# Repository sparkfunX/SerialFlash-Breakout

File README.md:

SerialFlash-Breakout
========================================

[*Serial Flash Breakout - Assembled*](https://www.sparkfun.com/products/17115)

[*Serial Flash Breakout - Bare*](https://www.sparkfun.com/products/17116)

Serial flash chips are everywhere and they're as useful as they are ubiquitous. If you've never used a serial flash device in your own projects, you should try it, because it's very handy to have a place to store things that don't fit in program memory. Things like sensor readings, long strings, and error logs can be hard to stow away on platforms that don't have a ton of in-built storage, which is where serial flash comes in. Simply write all of that data out over SPI for the flash chip to hold on to and retrieve it later! And thanks to their ubiquity, these chips have been largely standardized not only in terms of their software interface but also their hardware footprint, so there are plenty of serial flash chips to choose from.

SparkFun labored with love to design this board. Feel like supporting open source hardware? 
Buy a [board](https://www.sparkfun.com/products/17115) from SparkFun!

Repository Contents
-------------------

* **/Hardware** - Eagle design files (.brd, .sch)
* **/Documents** - Datasheet
* **/Production** - Production design files

License Information
-------------------

This product is _**open source**_! 

Please review the LICENSE.md file for license information. 

If you have any questions or concerns on licensing, please contact technical support on our [SparkFun forums](https://forum.sparkfun.com/viewforum.php?f=152).

Distributed as-is; no warranty is given.

- Your friends at SparkFun.

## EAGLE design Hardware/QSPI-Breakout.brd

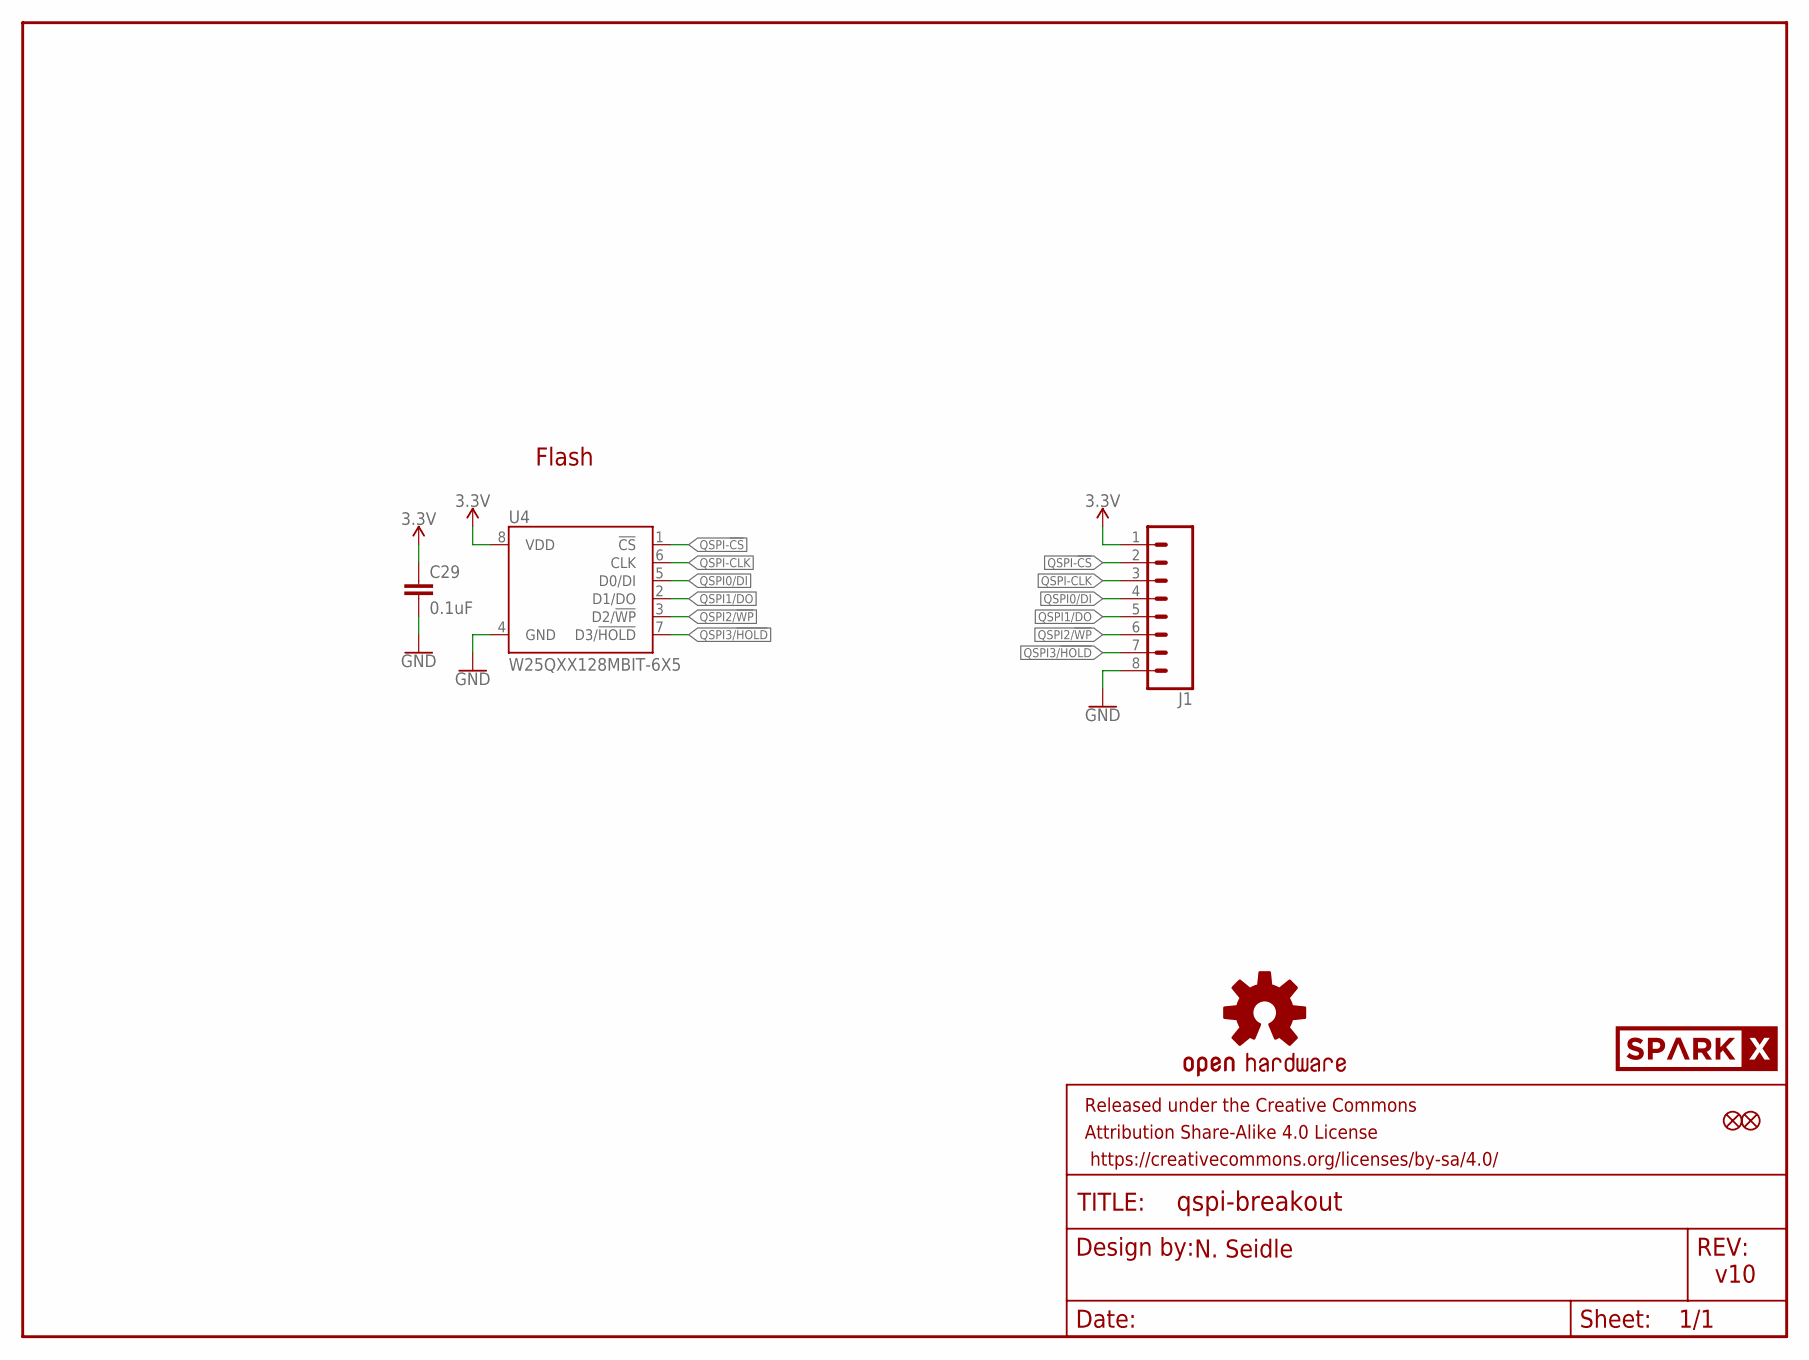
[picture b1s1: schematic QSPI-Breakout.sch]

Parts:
C29: 0.1uF; 0603
FD1, FD2: FIDUCIALUFIDUCIAL; FIDUCIAL-MICRO
FRAME2: FRAME-LETTER; CREATIVE_COMMONS
J1: CONN_08NO_SILK_DNP; 1X08_NO_SILK
LOGO2: OSHW-LOGONO_SILK; DUMMY
U4: W25QXX128MBIT-6X5; WSON-8-6X5-SKINNY_CENTERPAD
U$3: SPARKX-LOGO4; SPARKX-MEDIUM

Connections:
3.3V: C29.1, J1.1, U4.8 (VDD)
GND: C29.2, J1.8, U4.4 (GND)
QSPI0/DI: J1.4, U4.5 (D0/DI)
QSPI1/DO: J1.5, U4.2 (D1/DO)
QSPI2/!WP!: J1.6, U4.3 (D2/!WP!)
QSPI3/!HOLD!: J1.7, U4.7 (D3/!HOLD!)
QSPI-!CS!: J1.2, U4.1 (!CS!)
QSPI-CLK: J1.3, U4.6 (CLK)

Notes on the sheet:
v10
N. Seidle
Flash

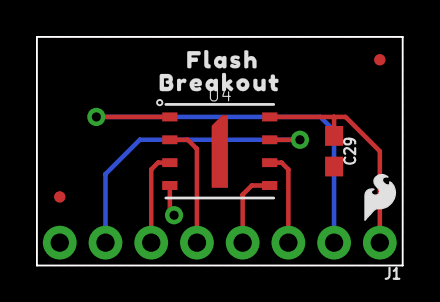
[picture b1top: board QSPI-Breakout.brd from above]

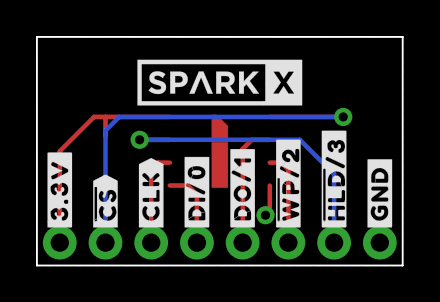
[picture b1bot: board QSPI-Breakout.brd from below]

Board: 2 copper layers, 20.3 x 12.7 mm, 19 parts (9 on the bottom side), 8 nets.

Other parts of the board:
U$1: BREAKOUT1
U$2: FLASH0
U$4: ##HLD##3#2
U$5: ##WP##2#3
U$6: SFE_LOGO_FLAME_.1
U$7: #3#3V#1
U$8: #CLK#6
U$9: #DI#0#5
U$10: #DO#1#4
U$11: #GND#0
U$12: ##CS##7

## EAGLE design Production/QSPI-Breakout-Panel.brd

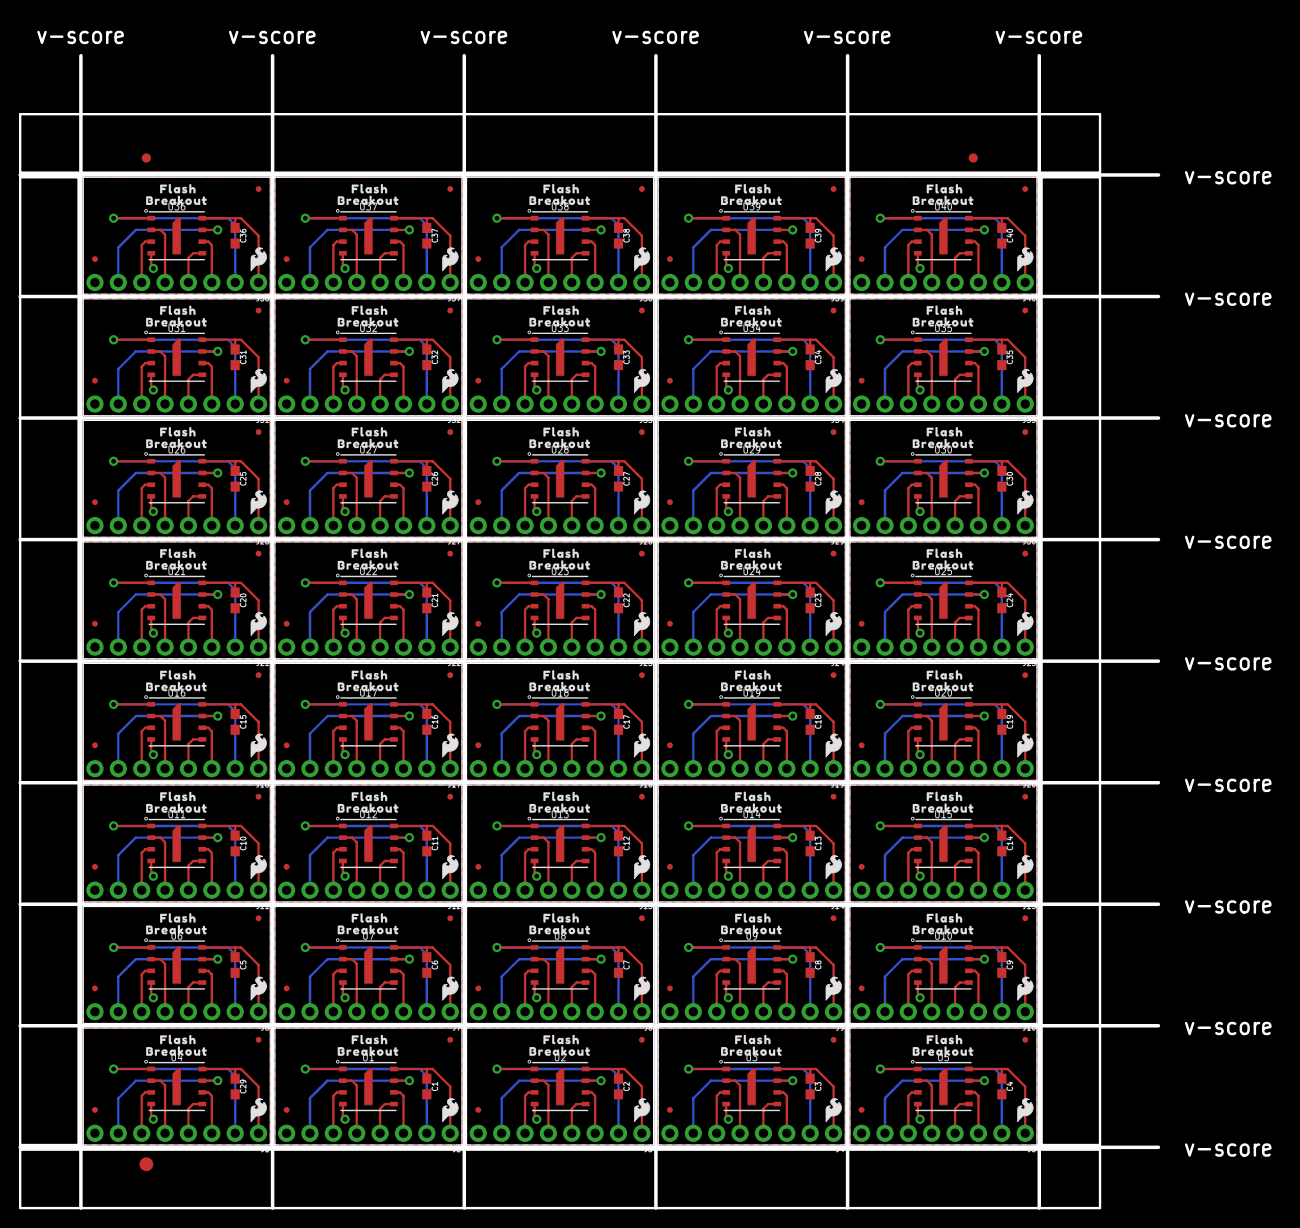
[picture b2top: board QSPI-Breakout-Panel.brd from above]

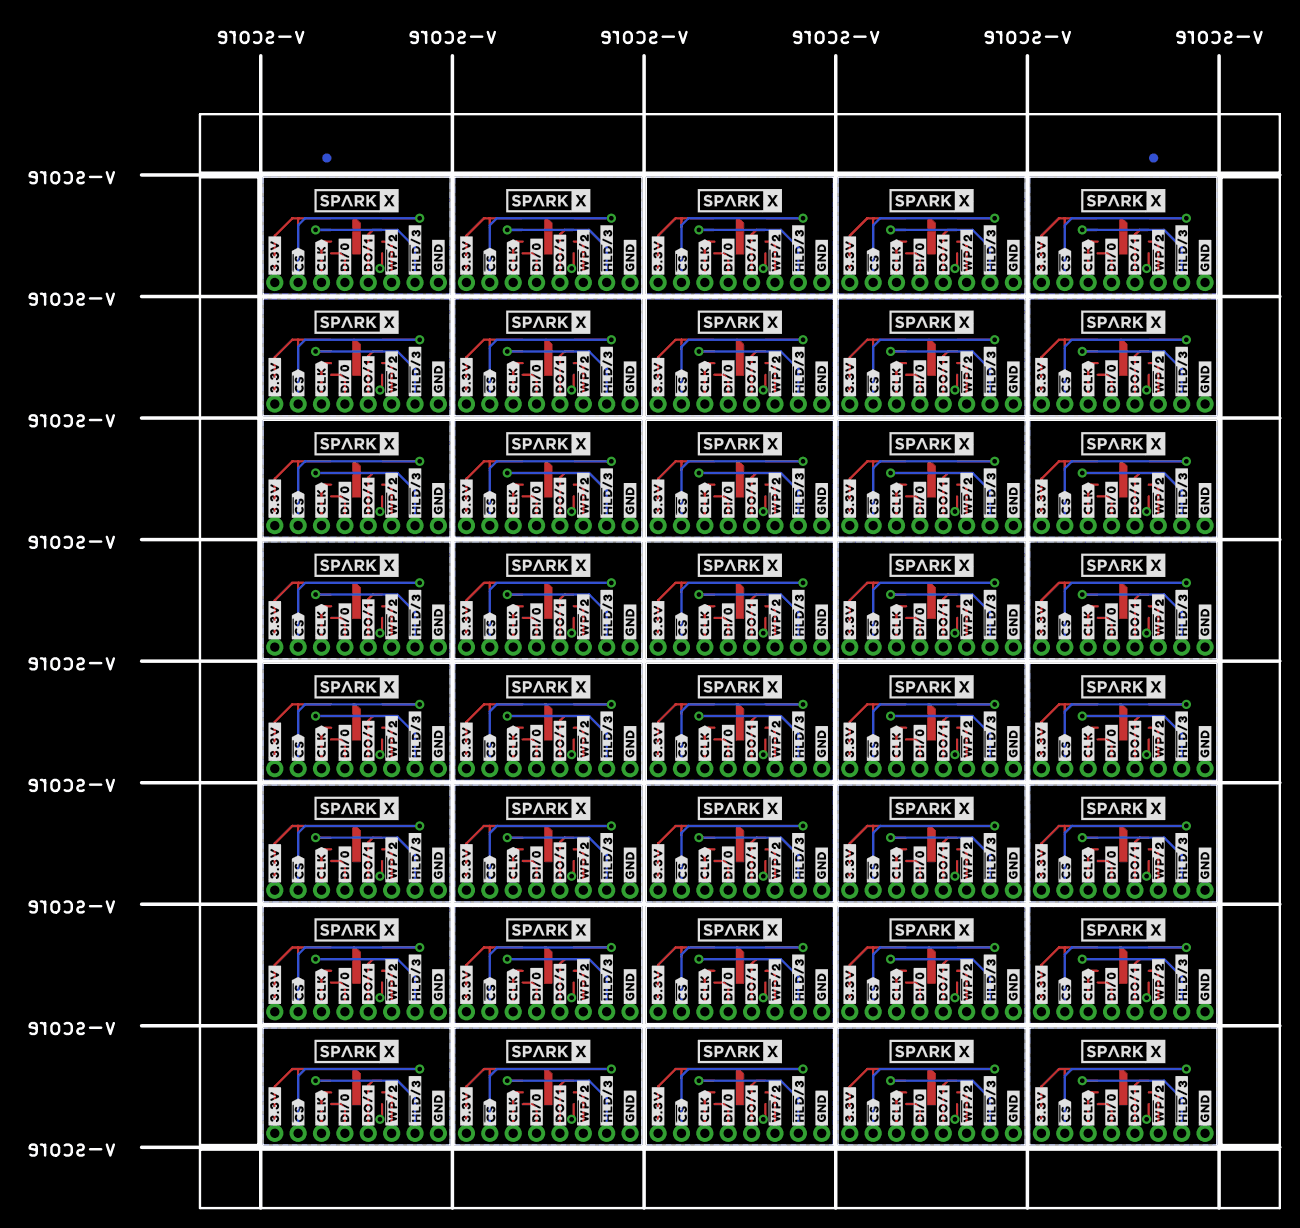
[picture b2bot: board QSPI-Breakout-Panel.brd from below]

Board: 2 copper layers, 123.7 x 125.2 mm, 725 parts (362 on the bottom side), 320 nets.

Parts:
C1, C2, C3, C4, C5, C6, C7, C8, C9, C10, C11, C12, C13, C14, C15, C16, C17, C18, C19, C20, C21, C22, C23, C24, C25, C26, C27, C28, C29, C30, C31, C32, C33, C34, C35, C36, C37, C38, C39, C40: 0.1uF; 0603
E$1, E$2, E$3, E$4: FIDUCIAL-1X2
E$5: FIDUCIAL-1.5X3
FD1, FD2, FD3, FD4, FD5, FD6, FD7, FD8, FD9, FD10, FD11, FD12, FD13, FD14, FD15, FD16, FD17, FD18, FD19, FD20, FD21, FD22, FD23, FD24, FD25, FD26, FD27, FD28, FD29, FD30, FD31, FD32, FD33, FD34, FD35, FD36, FD37, FD38, FD39, FD40, FD41, FD42, FD43, FD44, FD45, FD46, FD47, FD48, FD49, FD50, FD51, FD52, FD53, FD54, FD55, FD56, FD57, FD58, FD59, FD60, FD61, FD62, FD63, FD64, FD65, FD66, FD67, FD68, FD69, FD70, FD71, FD72, FD73, FD74, FD75, FD76, FD77, FD78, FD79, FD80: FIDUCIALUFIDUCIAL; FIDUCIAL-MICRO
J1, J2, J3, J4, J5, J6, J7, J8, J9, J10, J11, J12, J13, J14, J15, J16, J17, J18, J19, J20, J21, J22, J23, J24, J25, J26, J27, J28, J29, J30, J31, J32, J33, J34, J35, J36, J37, J38, J39, J40: 1X08_NO_SILK
LOGO1, LOGO2, LOGO3, LOGO4, LOGO5, LOGO6, LOGO7, LOGO8, LOGO9, LOGO10, LOGO11, LOGO12, LOGO13, LOGO14, LOGO15, LOGO16, LOGO17, LOGO18, LOGO19, LOGO20, LOGO21, LOGO22, LOGO23, LOGO24, LOGO25, LOGO26, LOGO27, LOGO28, LOGO29, LOGO30, LOGO31, LOGO32, LOGO33, LOGO34, LOGO35, LOGO36, LOGO37, LOGO38, LOGO39, LOGO40: OSHW-LOGONO_SILK; DUMMY
U1, U2, U3, U4, U5, U6, U7, U8, U9, U10, U11, U12, U13, U14, U15, U16, U17, U18, U19, U20, U21, U22, U23, U24, U25, U26, U27, U28, U29, U30, U31, U32, U33, U34, U35, U36, U37, U38, U39, U40: W25QXX128MBIT-6X5; WSON-8-6X5-SKINNY_CENTERPAD
U$1, U$14, U$26, U$38, U$50, U$62, U$74, U$86, U$98, U$110, U$122, U$134, U$146, U$158, U$170, U$182, U$194, U$206, U$218, U$230, U$242, U$254, U$266, U$278, U$290, U$302, U$314, U$326, U$338, U$350, U$362, U$374, U$386, U$398, U$410, U$422, U$434, U$446, U$458, U$470: BREAKOUT1
U$2, U$15, U$27, U$39, U$51, U$63, U$75, U$87, U$99, U$111, U$123, U$135, U$147, U$159, U$171, U$183, U$195, U$207, U$219, U$231, U$243, U$255, U$267, U$279, U$291, U$303, U$315, U$327, U$339, U$351, U$363, U$375, U$387, U$399, U$411, U$423, U$435, U$447, U$459, U$471: FLASH0
U$3, U$24, U$36, U$48, U$60, U$72, U$84, U$96, U$108, U$120, U$132, U$144, U$156, U$168, U$180, U$192, U$204, U$216, U$228, U$240, U$252, U$264, U$276, U$288, U$300, U$312, U$324, U$336, U$348, U$360, U$372, U$384, U$396, U$408, U$420, U$432, U$444, U$456, U$468, U$480: SPARKX-LOGO4; SPARKX-MEDIUM
U$4, U$16, U$28, U$40, U$52, U$64, U$76, U$88, U$100, U$112, U$124, U$136, U$148, U$160, U$172, U$184, U$196, U$208, U$220, U$232, U$244, U$256, U$268, U$280, U$292, U$304, U$316, U$328, U$340, U$352, U$364, U$376, U$388, U$400, U$412, U$424, U$436, U$448, U$460, U$472: ##HLD##3#2
U$5, U$17, U$29, U$41, U$53, U$65, U$77, U$89, U$101, U$113, U$125, U$137, U$149, U$161, U$173, U$185, U$197, U$209, U$221, U$233, U$245, U$257, U$269, U$281, U$293, U$305, U$317, U$329, U$341, U$353, U$365, U$377, U$389, U$401, U$413, U$425, U$437, U$449, U$461, U$473: ##WP##2#3
U$6, U$13, U$25, U$37, U$49, U$61, U$73, U$85, U$97, U$109, U$121, U$133, U$145, U$157, U$169, U$181, U$193, U$205, U$217, U$229, U$241, U$253, U$265, U$277, U$289, U$301, U$313, U$325, U$337, U$349, U$361, U$373, U$385, U$397, U$409, U$421, U$433, U$445, U$457, U$469: SFE_LOGO_FLAME_.1
U$7, U$18, U$30, U$42, U$54, U$66, U$78, U$90, U$102, U$114, U$126, U$138, U$150, U$162, U$174, U$186, U$198, U$210, U$222, U$234, U$246, U$258, U$270, U$282, U$294, U$306, U$318, U$330, U$342, U$354, U$366, U$378, U$390, U$402, U$414, U$426, U$438, U$450, U$462, U$474: #3#3V#1
U$8, U$19, U$31, U$43, U$55, U$67, U$79, U$91, U$103, U$115, U$127, U$139, U$151, U$163, U$175, U$187, U$199, U$211, U$223, U$235, U$247, U$259, U$271, U$283, U$295, U$307, U$319, U$331, U$343, U$355, U$367, U$379, U$391, U$403, U$415, U$427, U$439, U$451, U$463, U$475: #CLK#6
U$9, U$20, U$32, U$44, U$56, U$68, U$80, U$92, U$104, U$116, U$128, U$140, U$152, U$164, U$176, U$188, U$200, U$212, U$224, U$236, U$248, U$260, U$272, U$284, U$296, U$308, U$320, U$332, U$344, U$356, U$368, U$380, U$392, U$404, U$416, U$428, U$440, U$452, U$464, U$476: #DI#0#5
U$10, U$21, U$33, U$45, U$57, U$69, U$81, U$93, U$105, U$117, U$129, U$141, U$153, U$165, U$177, U$189, U$201, U$213, U$225, U$237, U$249, U$261, U$273, U$285, U$297, U$309, U$321, U$333, U$345, U$357, U$369, U$381, U$393, U$405, U$417, U$429, U$441, U$453, U$465, U$477: #DO#1#4
U$11, U$22, U$34, U$46, U$58, U$70, U$82, U$94, U$106, U$118, U$130, U$142, U$154, U$166, U$178, U$190, U$202, U$214, U$226, U$238, U$250, U$262, U$274, U$286, U$298, U$310, U$322, U$334, U$346, U$358, U$370, U$382, U$394, U$406, U$418, U$430, U$442, U$454, U$466, U$478: #GND#0
U$12, U$23, U$35, U$47, U$59, U$71, U$83, U$95, U$107, U$119, U$131, U$143, U$155, U$167, U$179, U$191, U$203, U$215, U$227, U$239, U$251, U$263, U$275, U$287, U$299, U$311, U$323, U$335, U$347, U$359, U$371, U$383, U$395, U$407, U$419, U$431, U$443, U$455, U$467, U$479: ##CS##7

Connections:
3.3V: C29.1, J1.1, U4.8
3.3V1: C1.1, J2.1, U1.8
3.3V2: C2.1, J3.1, U2.8
3.3V3: C3.1, J4.1, U3.8
3.3V4: C4.1, J5.1, U5.8
3.3V5: C5.1, J6.1, U6.8
3.3V6: C6.1, J7.1, U7.8
3.3V7: C7.1, J8.1, U8.8
3.3V8: C8.1, J9.1, U9.8
3.3V9: C9.1, J10.1, U10.8
3.3V10: C10.1, J11.1, U11.8
3.3V11: C11.1, J12.1, U12.8
3.3V12: C12.1, J13.1, U13.8
3.3V13: C13.1, J14.1, U14.8
3.3V14: C14.1, J15.1, U15.8
3.3V15: C15.1, J16.1, U16.8
3.3V16: C16.1, J17.1, U17.8
3.3V17: C17.1, J18.1, U18.8
3.3V18: C18.1, J19.1, U19.8
3.3V19: C19.1, J20.1, U20.8
3.3V20: C20.1, J21.1, U21.8
3.3V21: C21.1, J22.1, U22.8
3.3V22: C22.1, J23.1, U23.8
3.3V23: C23.1, J24.1, U24.8
3.3V24: C24.1, J25.1, U25.8
3.3V25: C25.1, J26.1, U26.8
3.3V26: C26.1, J27.1, U27.8
3.3V27: C27.1, J28.1, U28.8
3.3V28: C28.1, J29.1, U29.8
3.3V29: C30.1, J30.1, U30.8
3.3V30: C31.1, J31.1, U31.8
3.3V31: C32.1, J32.1, U32.8
3.3V32: C33.1, J33.1, U33.8
3.3V33: C34.1, J34.1, U34.8
3.3V34: C35.1, J35.1, U35.8
3.3V35: C36.1, J36.1, U36.8
3.3V36: C37.1, J37.1, U37.8
3.3V37: C38.1, J38.1, U38.8
3.3V38: C39.1, J39.1, U39.8
3.3V39: C40.1, J40.1, U40.8
GND: C29.2, J1.8, U4.4
GND1: C1.2, J2.8, U1.4
GND2: C2.2, J3.8, U2.4
GND3: C3.2, J4.8, U3.4
GND4: C4.2, J5.8, U5.4
GND5: C5.2, J6.8, U6.4
GND6: C6.2, J7.8, U7.4
GND7: C7.2, J8.8, U8.4
GND8: C8.2, J9.8, U9.4
GND9: C9.2, J10.8, U10.4
GND10: C10.2, J11.8, U11.4
GND11: C11.2, J12.8, U12.4
GND12: C12.2, J13.8, U13.4
GND13: C13.2, J14.8, U14.4
GND14: C14.2, J15.8, U15.4
GND15: C15.2, J16.8, U16.4
GND16: C16.2, J17.8, U17.4
GND17: C17.2, J18.8, U18.4
GND18: C18.2, J19.8, U19.4
GND19: C19.2, J20.8, U20.4
GND20: C20.2, J21.8, U21.4
GND21: C21.2, J22.8, U22.4
GND22: C22.2, J23.8, U23.4
GND23: C23.2, J24.8, U24.4
GND24: C24.2, J25.8, U25.4
GND25: C25.2, J26.8, U26.4
GND26: C26.2, J27.8, U27.4
GND27: C27.2, J28.8, U28.4
GND28: C28.2, J29.8, U29.4
GND29: C30.2, J30.8, U30.4
GND30: C31.2, J31.8, U31.4
GND31: C32.2, J32.8, U32.4
GND32: C33.2, J33.8, U33.4
GND33: C34.2, J34.8, U34.4
GND34: C35.2, J35.8, U35.4
GND35: C36.2, J36.8, U36.4
GND36: C37.2, J37.8, U37.4
GND37: C38.2, J38.8, U38.4
GND38: C39.2, J39.8, U39.4
GND39: C40.2, J40.8, U40.4
QSPI0/DI: J1.4, U4.5
QSPI0/DI1: J2.4, U1.5
QSPI0/DI2: J3.4, U2.5
QSPI0/DI3: J4.4, U3.5
QSPI0/DI4: J5.4, U5.5
QSPI0/DI5: J6.4, U6.5
QSPI0/DI6: J7.4, U7.5
QSPI0/DI7: J8.4, U8.5
QSPI0/DI8: J9.4, U9.5
QSPI0/DI9: J10.4, U10.5
QSPI0/DI10: J11.4, U11.5
QSPI0/DI11: J12.4, U12.5
QSPI0/DI12: J13.4, U13.5
QSPI0/DI13: J14.4, U14.5
QSPI0/DI14: J15.4, U15.5
QSPI0/DI15: J16.4, U16.5
QSPI0/DI16: J17.4, U17.5
QSPI0/DI17: J18.4, U18.5
QSPI0/DI18: J19.4, U19.5
QSPI0/DI19: J20.4, U20.5
QSPI0/DI20: J21.4, U21.5
QSPI0/DI21: J22.4, U22.5
QSPI0/DI22: J23.4, U23.5
QSPI0/DI23: J24.4, U24.5
QSPI0/DI24: J25.4, U25.5
QSPI0/DI25: J26.4, U26.5
QSPI0/DI26: J27.4, U27.5
QSPI0/DI27: J28.4, U28.5
QSPI0/DI28: J29.4, U29.5
QSPI0/DI29: J30.4, U30.5
QSPI0/DI30: J31.4, U31.5
QSPI0/DI31: J32.4, U32.5
QSPI0/DI32: J33.4, U33.5
QSPI0/DI33: J34.4, U34.5
QSPI0/DI34: J35.4, U35.5
QSPI0/DI35: J36.4, U36.5
QSPI0/DI36: J37.4, U37.5
QSPI0/DI37: J38.4, U38.5
QSPI0/DI38: J39.4, U39.5
QSPI0/DI39: J40.4, U40.5
QSPI1/DO: J1.5, U4.2
QSPI1/DO1: J2.5, U1.2
QSPI1/DO2: J3.5, U2.2
QSPI1/DO3: J4.5, U3.2
QSPI1/DO4: J5.5, U5.2
QSPI1/DO5: J6.5, U6.2
QSPI1/DO6: J7.5, U7.2
QSPI1/DO7: J8.5, U8.2
QSPI1/DO8: J9.5, U9.2
QSPI1/DO9: J10.5, U10.2
QSPI1/DO10: J11.5, U11.2
QSPI1/DO11: J12.5, U12.2
QSPI1/DO12: J13.5, U13.2
QSPI1/DO13: J14.5, U14.2
QSPI1/DO14: J15.5, U15.2
QSPI1/DO15: J16.5, U16.2
QSPI1/DO16: J17.5, U17.2
QSPI1/DO17: J18.5, U18.2
QSPI1/DO18: J19.5, U19.2
QSPI1/DO19: J20.5, U20.2
QSPI1/DO20: J21.5, U21.2
QSPI1/DO21: J22.5, U22.2
QSPI1/DO22: J23.5, U23.2
QSPI1/DO23: J24.5, U24.2
QSPI1/DO24: J25.5, U25.2
QSPI1/DO25: J26.5, U26.2
QSPI1/DO26: J27.5, U27.2
QSPI1/DO27: J28.5, U28.2
QSPI1/DO28: J29.5, U29.2
QSPI1/DO29: J30.5, U30.2
QSPI1/DO30: J31.5, U31.2
QSPI1/DO31: J32.5, U32.2
QSPI1/DO32: J33.5, U33.2
QSPI1/DO33: J34.5, U34.2
QSPI1/DO34: J35.5, U35.2
QSPI1/DO35: J36.5, U36.2
QSPI1/DO36: J37.5, U37.2
QSPI1/DO37: J38.5, U38.2
QSPI1/DO38: J39.5, U39.2
QSPI1/DO39: J40.5, U40.2
QSPI2/!WP!: J1.6, U4.3
QSPI2/!WP!1: J2.6, U1.3
QSPI2/!WP!2: J3.6, U2.3
QSPI2/!WP!3: J4.6, U3.3
QSPI2/!WP!4: J5.6, U5.3
QSPI2/!WP!5: J6.6, U6.3
QSPI2/!WP!6: J7.6, U7.3
QSPI2/!WP!7: J8.6, U8.3
QSPI2/!WP!8: J9.6, U9.3
QSPI2/!WP!9: J10.6, U10.3
QSPI2/!WP!10: J11.6, U11.3
QSPI2/!WP!11: J12.6, U12.3
QSPI2/!WP!12: J13.6, U13.3
QSPI2/!WP!13: J14.6, U14.3
QSPI2/!WP!14: J15.6, U15.3
QSPI2/!WP!15: J16.6, U16.3
QSPI2/!WP!16: J17.6, U17.3
QSPI2/!WP!17: J18.6, U18.3
QSPI2/!WP!18: J19.6, U19.3
QSPI2/!WP!19: J20.6, U20.3
QSPI2/!WP!20: J21.6, U21.3
QSPI2/!WP!21: J22.6, U22.3
QSPI2/!WP!22: J23.6, U23.3
QSPI2/!WP!23: J24.6, U24.3
QSPI2/!WP!24: J25.6, U25.3
QSPI2/!WP!25: J26.6, U26.3
QSPI2/!WP!26: J27.6, U27.3
QSPI2/!WP!27: J28.6, U28.3
QSPI2/!WP!28: J29.6, U29.3
QSPI2/!WP!29: J30.6, U30.3
QSPI2/!WP!30: J31.6, U31.3
QSPI2/!WP!31: J32.6, U32.3
QSPI2/!WP!32: J33.6, U33.3
QSPI2/!WP!33: J34.6, U34.3
QSPI2/!WP!34: J35.6, U35.3
QSPI2/!WP!35: J36.6, U36.3
QSPI2/!WP!36: J37.6, U37.3
QSPI2/!WP!37: J38.6, U38.3
QSPI2/!WP!38: J39.6, U39.3
QSPI2/!WP!39: J40.6, U40.3
QSPI3/!HOLD!: J1.7, U4.7
QSPI3/!HOLD!1: J2.7, U1.7
QSPI3/!HOLD!2: J3.7, U2.7
QSPI3/!HOLD!3: J4.7, U3.7
QSPI3/!HOLD!4: J5.7, U5.7
QSPI3/!HOLD!5: J6.7, U6.7
QSPI3/!HOLD!6: J7.7, U7.7
QSPI3/!HOLD!7: J8.7, U8.7
QSPI3/!HOLD!8: J9.7, U9.7
QSPI3/!HOLD!9: J10.7, U10.7
QSPI3/!HOLD!10: J11.7, U11.7
QSPI3/!HOLD!11: J12.7, U12.7
QSPI3/!HOLD!12: J13.7, U13.7
QSPI3/!HOLD!13: J14.7, U14.7
QSPI3/!HOLD!14: J15.7, U15.7
QSPI3/!HOLD!15: J16.7, U16.7
QSPI3/!HOLD!16: J17.7, U17.7
QSPI3/!HOLD!17: J18.7, U18.7
QSPI3/!HOLD!18: J19.7, U19.7
QSPI3/!HOLD!19: J20.7, U20.7
QSPI3/!HOLD!20: J21.7, U21.7
QSPI3/!HOLD!21: J22.7, U22.7
QSPI3/!HOLD!22: J23.7, U23.7
QSPI3/!HOLD!23: J24.7, U24.7
QSPI3/!HOLD!24: J25.7, U25.7
QSPI3/!HOLD!25: J26.7, U26.7
QSPI3/!HOLD!26: J27.7, U27.7
QSPI3/!HOLD!27: J28.7, U28.7
QSPI3/!HOLD!28: J29.7, U29.7
QSPI3/!HOLD!29: J30.7, U30.7
QSPI3/!HOLD!30: J31.7, U31.7
QSPI3/!HOLD!31: J32.7, U32.7
QSPI3/!HOLD!32: J33.7, U33.7
QSPI3/!HOLD!33: J34.7, U34.7
QSPI3/!HOLD!34: J35.7, U35.7
QSPI3/!HOLD!35: J36.7, U36.7
QSPI3/!HOLD!36: J37.7, U37.7
QSPI3/!HOLD!37: J38.7, U38.7
QSPI3/!HOLD!38: J39.7, U39.7
QSPI3/!HOLD!39: J40.7, U40.7
QSPI-!CS!: J1.2, U4.1
QSPI-!CS!1: J2.2, U1.1
QSPI-!CS!2: J3.2, U2.1
QSPI-!CS!3: J4.2, U3.1
QSPI-!CS!4: J5.2, U5.1
QSPI-!CS!5: J6.2, U6.1
QSPI-!CS!6: J7.2, U7.1
QSPI-!CS!7: J8.2, U8.1
QSPI-!CS!8: J9.2, U9.1
QSPI-!CS!9: J10.2, U10.1
QSPI-!CS!10: J11.2, U11.1
QSPI-!CS!11: J12.2, U12.1
QSPI-!CS!12: J13.2, U13.1
QSPI-!CS!13: J14.2, U14.1
QSPI-!CS!14: J15.2, U15.1
QSPI-!CS!15: J16.2, U16.1
QSPI-!CS!16: J17.2, U17.1
QSPI-!CS!17: J18.2, U18.1
QSPI-!CS!18: J19.2, U19.1
QSPI-!CS!19: J20.2, U20.1
QSPI-!CS!20: J21.2, U21.1
QSPI-!CS!21: J22.2, U22.1
QSPI-!CS!22: J23.2, U23.1
QSPI-!CS!23: J24.2, U24.1
QSPI-!CS!24: J25.2, U25.1
QSPI-!CS!25: J26.2, U26.1
QSPI-!CS!26: J27.2, U27.1
QSPI-!CS!27: J28.2, U28.1
QSPI-!CS!28: J29.2, U29.1
QSPI-!CS!29: J30.2, U30.1
QSPI-!CS!30: J31.2, U31.1
QSPI-!CS!31: J32.2, U32.1
QSPI-!CS!32: J33.2, U33.1
QSPI-!CS!33: J34.2, U34.1
QSPI-!CS!34: J35.2, U35.1
QSPI-!CS!35: J36.2, U36.1
QSPI-!CS!36: J37.2, U37.1
QSPI-!CS!37: J38.2, U38.1
QSPI-!CS!38: J39.2, U39.1
QSPI-!CS!39: J40.2, U40.1
QSPI-CLK: J1.3, U4.6
QSPI-CLK1: J2.3, U1.6
QSPI-CLK2: J3.3, U2.6
QSPI-CLK3: J4.3, U3.6
QSPI-CLK4: J5.3, U5.6
QSPI-CLK5: J6.3, U6.6
QSPI-CLK6: J7.3, U7.6
QSPI-CLK7: J8.3, U8.6
QSPI-CLK8: J9.3, U9.6
QSPI-CLK9: J10.3, U10.6
QSPI-CLK10: J11.3, U11.6
QSPI-CLK11: J12.3, U12.6
QSPI-CLK12: J13.3, U13.6
QSPI-CLK13: J14.3, U14.6
QSPI-CLK14: J15.3, U15.6
QSPI-CLK15: J16.3, U16.6
QSPI-CLK16: J17.3, U17.6
QSPI-CLK17: J18.3, U18.6
QSPI-CLK18: J19.3, U19.6
QSPI-CLK19: J20.3, U20.6
QSPI-CLK20: J21.3, U21.6
QSPI-CLK21: J22.3, U22.6
QSPI-CLK22: J23.3, U23.6
QSPI-CLK23: J24.3, U24.6
QSPI-CLK24: J25.3, U25.6
QSPI-CLK25: J26.3, U26.6
QSPI-CLK26: J27.3, U27.6
QSPI-CLK27: J28.3, U28.6
QSPI-CLK28: J29.3, U29.6
QSPI-CLK29: J30.3, U30.6
QSPI-CLK30: J31.3, U31.6
QSPI-CLK31: J32.3, U32.6
QSPI-CLK32: J33.3, U33.6
QSPI-CLK33: J34.3, U34.6
QSPI-CLK34: J35.3, U35.6
QSPI-CLK35: J36.3, U36.6
QSPI-CLK36: J37.3, U37.6
QSPI-CLK37: J38.3, U38.6
QSPI-CLK38: J39.3, U39.6
QSPI-CLK39: J40.3, U40.6

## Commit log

2020-09-01 Added datasheet to repo
2020-09-03 Update datasheet
2020-09-08 housecleaning!
2020-11-20 Create License.md
    Adding License

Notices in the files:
parts and their libraries:
SparkFun-Aesthetics: Licensing: Creative Commons ShareAlike 4.0 International - https://creativecommons.org/licenses/by-sa/4.0
SparkFun-Aesthetics: Released under the Creative Commons Attribution Share-Alike 4.0 License
SparkFun-Aesthetics: https://creativecommons.org/licenses/by-sa/4.0
